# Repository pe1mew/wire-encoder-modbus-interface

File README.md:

# Wire Encoder Modbus Interface

A CH32V003-based interface board that measures **how far a window is open**
and publishes it on **Modbus RTU over RS-485**, powered by 24 V passive PoE
and designed for daisy-chained field buses.

The measurement comes from a **draw-wire encoder**: a spring-loaded drum
pays out a steel wire attached to the moving window frame, and the drum
turns a **10 kΩ potentiometer**. The wiper voltage is therefore an absolute
measure of the opening — valid the instant power returns, with no homing
move and no count to lose.

Two end-of-travel switches report that the window has reached a mechanical
stop, read as a supervised resistor ladder that also monitors its own cable.

One firmware build, addressed by a PC1 solder jumper:

| Jumper open | Jumper bridged |
|---|---|
| **40** | 45 |

The 40/45 pair is deliberately clear of the sibling
[`windmeters-modbus-interface`](https://github.com/pe1mew/windmeters-modbus-interface)
family (30–37), so both can share one RS-485 segment.

## Project status (2026-09-05)

| Area | State |
|---|---|
| Requirements | [`design/TDS.md`](design/TDS.md) **v0.7** — **79 requirements** (28 FR-MB, 20 FR-S, 23 FR-E, 8 NFR), every one traced to a test row and **gate-enforced** by `software/hil/acceptance/test_traceability.py` |
| Drivers | Modbus RTU + debug UART carried over HIL-verified; the encoder driver (`software/drivers/wire_encoder/`) is **written, verified and integrated** |
| Product firmware | **Complete.** Integration stages **A–F done** ([`design/integrationPlan.md`](design/integrationPlan.md)) — measurement, averaging, persistence and sensing health. 6 364 B flash (44 %), 1 108 B RAM (62 %). A healthy device reports status `0x0000` |
| Hardware/HIL | Schematic and PCB layout in `hardware/KiCad/`; the build under test is still a **breadboard**, so every Group A result carries that caveat. HIL rig complete: ADALM2000 RS-485 master, Saleae Logic16, and a built window emulator |
| Testing | 3 host suites (`scale`, `avg`, `health`), 27 HIL scripts, 11 acceptance tests. Results in [`software/hil/testReport.md`](software/hil/testReport.md) |
| Blocked | Four items, all on **instruments, not code**: adjustable PSU (±15 % supply margin, TP-A03/TP-B23 — the tightest unmeasured number), a PCB (TP-B36), a precision resistance box (FR-E03), a 5 ms bounce injector (FR-E15) |
| Release | No firmware version tagged yet; `fw-v1` is a candidate pending the above ([`software/firmware/RELEASES.md`](software/firmware/RELEASES.md)) |

## Hardware

The board reuses the sibling project's design wholesale apart from the
sensor front-end:

- **MCU**: WCH CH32V003J4M6 (RISC-V, SOP-8, 16 KB flash / 2 KB RAM). The
  8-pin package drives the whole design: single-wire UART discipline, remap
  tricks, and a zero-interrupt firmware architecture
  ([`design/softwareArchitecture.md`](design/softwareArchitecture.md)).
- **RS-485**: MAX3485; DI+RO tied to PD6, DE+R̄Ē tied to PC2 with a 10 k
  pull-down (keeps the bus safe during reset/flashing); 120 Ω terminator
  behind a solder jumper; A/B fail-safe bias; SM712 TVS.
- **Power**: 24 V passive PoE on the spare pairs (4/5 = +, 7/8 = −) →
  DB207 bridge (polarity protection only) → HLK-K7803 buck → 3.3 V.
- **Sensor front-end**: the potentiometer wiper on PA2 (ADC ch0), read
  ratiometrically against VDD — no external reference, so supply ripple
  cancels. The end-switch ladder is on PC4 (ADC ch2).

**The pin budget is the binding constraint.** The SOP-8 package bonds
several GPIO onto shared pins (pin 1 is PD6 *and* PA1; pin 8 is PD1, PD4
*and* PD5), leaving **six physical I/O pins — and every one is committed**:
Modbus data, the wiper, DE/RE, the address jumper, the end-switch ladder,
SWIO. Note PC1 and PC4 are assigned the reverse of the obvious way: PC4
carries an ADC channel and PC1 does not, so the analog pin goes to the
switch loop and the boot-time address jumper takes the digital pin. Any
front-end idea that needs another pin does not fit. See
[`design/TDS.md`](design/TDS.md) §4.2.

## Modbus register map (summary)

12 input registers (FC04) and 6 holding registers (FC03/06/16). Inputs:
instantaneous and averaged opening, the minimum/maximum of the current
averaging window, the raw ADC code, status bits (including end-of-travel
reached and switch-loop fault), identification (build + firmware version),
uptime, CRC/served counters, seconds-since-last-valid-reading, and movement
rate. Holdings: zero offset,
measurement window, averaging window, full travel, and the two-point raw
calibration (raw code closed / raw code fully open) — so one image serves
any window, calibrated in the field over Modbus. All persisted in flash
across reset/power-loss; the defaults apply only on first boot / erased
store. The authoritative map with ranges, defaults and requirement IDs is
[`design/TDS.md`](design/TDS.md) §2.7/§2.8.

## Repository layout

| Path | Contents |
|---|---|
| [`design/`](design/README.md) | The design-document chain (index in [`design/README.md`](design/README.md)): scratchBook → description → TDS → softwareArchitecture (+ UML diagrams in `design/diagrams/`) → driverDevelopment → integrationPlan |
| `hardware/KiCad/` | Schematic + PCB (KiCad); symbol libraries as git submodules |
| `hardware/Documentation/` | Component datasheets (HLK-K78xx, DB20x, MAX3483/85, Kradex enclosure) |
| `software/firmware/` | Product firmware (PlatformIO + ch32v003fun): one release build, plus a bench-only test build |
| `software/drivers/` | Standalone driver projects with HIL test shells (the verified libraries the product references in place) |
| `software/hil/` | Scripted hardware-in-the-loop harness: Saleae Logic 2 (MCP) + ADALM2000 (libm2k) + `acceptance/` pytest suite |
| `Doxyfile` | Doxygen config — builds a single site (design docs + API reference) with this README as the landing page |
| `documentation/` | Chip pinout, programmer manual, and sensor reference material |

Clone with submodules:

```sh
git clone --recurse-submodules https://github.com/pe1mew/wire-encoder-modbus-interface.git
```

## Building and flashing

Requires [PlatformIO](https://platformio.org/) and a WCH-LinkE on SWIO.

```sh
cd software/firmware
pio run                            # the release build
pio run -t upload                  # flash via WCH-LinkE
```

`encoder_test` adds bench-only hooks — never release that binary. Resource
ceilings (14 336 B flash / 1 792 B RAM, NFR-RES01) are enforced as hard
build gates.
The firmware version byte lives in `src/version.h`; the release process is
documented in `RELEASES.md`.

## Testing

- **Acceptance suite** (bench: Saleae Logic 2 with its MCP server, ADALM2000,
  WCH-LinkE, TTL Modbus rig):

  ```sh
  cd software/hil/acceptance
  ..\.venv-m2k\Scripts\python.exe -m pytest .
  ```

  Only the build-gate rows are populated so far; the protocol and
  measurement rows arrive with the driver work. See
  [`software/hil/README.md`](software/hil/README.md) for instrument setup,
  wiring, and the bench-quirk catalogue.

## Documentation

- **What the device does** — [`design/description.md`](design/description.md)
  is the functional description in prose: sensing principle, what it
  reports, commissioning, fault behaviour, and the boundary of what it does
  not do. Start there.
- **Design record** — [`design/README.md`](design/README.md) indexes the
  document chain (requirements → architecture → drivers → integration) and
  the UML diagrams.
- **API + design site** — the firmware headers/sources carry full Doxygen,
  and [`Doxyfile`](Doxyfile) folds the design docs in as pages with this
  README as the landing page. Build the browsable HTML with:

  ```sh
  doxygen Doxyfile        # output in documentation/doxygen/html/index.html
  ```

## Related repositories

- [`pe1mew/windmeters-modbus-interface`](https://github.com/pe1mew/windmeters-modbus-interface) —
  the sibling project this repository is derived from: same MCU, same
  RS-485 front-end, same zero-ISR architecture, and the same potentiometer
  reading topology. Its Modbus RTU driver, board/persistence modules and
  HIL harness are carried over here, and its `design/` chain is the
  reference for anything not yet written down.
- [`pe1mew/windmeters-modbus-interface-tester`](https://github.com/pe1mew/windmeters-modbus-interface-tester) —
  the Modbus RTU master bench tool (M5Stack AtomS3 + RS-485) used to
  exercise devices in this family.

## License

Software is provided under a Source-Available Non-Commercial License;
documentation and images under CC BY-NC-ND 4.0. See [LICENSE](LICENSE) and
[license.md](license.md). Third-party datasheets and KiCad library
submodules remain under their owners' terms.

## Author

Remko Welling (PE1MEW)

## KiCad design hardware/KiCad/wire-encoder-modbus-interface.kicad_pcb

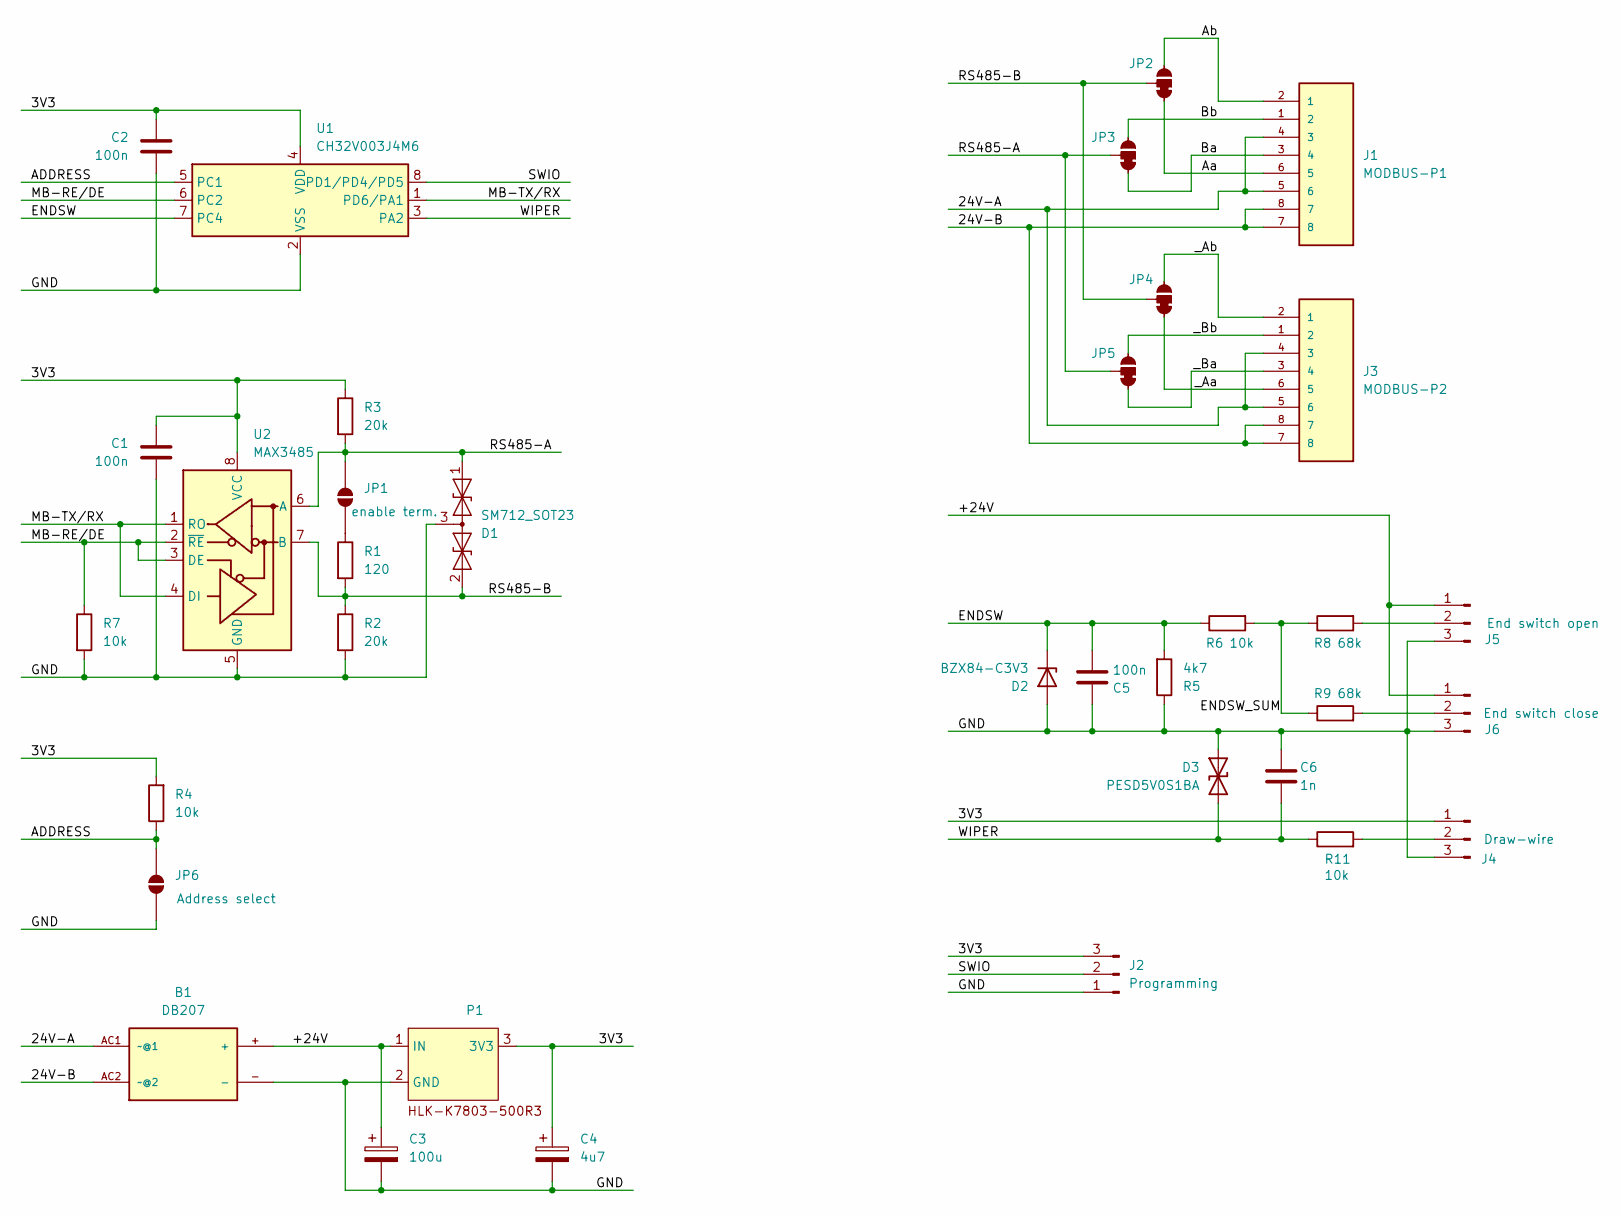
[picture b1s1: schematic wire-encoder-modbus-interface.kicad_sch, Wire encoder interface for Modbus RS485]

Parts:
B1: DB207; DB207-DIP-4
C1, C2, C5: 100n; C_1206_3216Metric_Pad1.33x1.80mm_HandSolder
C3: 100u; CP_Radial_D8.0mm_P5.00mm
C4: 4u7; CP_Radial_D5.0mm_P2.50mm
C6: 1n; C_1206_3216Metric_Pad1.33x1.80mm_HandSolder
D1: SM712_SOT23; SOT-23
D2: BZX84-C3V3; SOT-23
D3: PESD5V0S1BA; D_SOD-323_HandSoldering
J1: MODBUS-P1; CONN_215877-1; PARTREV AF1
J2: Programming; PinHeader_1x03_P2.54mm_Vertical
J3: MODBUS-P2; CONN_215877-1; PARTREV AF1
J4: Draw-wire; JST_NV_B03P-NV_1x03_P5.00mm_Vertical
J5: End switch open; JST_NV_B03P-NV_1x03_P5.00mm_Vertical
J6: End switch close; JST_NV_B03P-NV_1x03_P5.00mm_Vertical
JP1: enable term.; SolderJumper-2_P1.3mm_Open_Pad1.0x1.5mm
JP2, JP3, JP4, JP5: SolderJumper-3_P1.3mm_Bridged12_Pad1.0x1.5mm_NumberLabels
JP6: Address select; SolderJumper-2_P1.3mm_Open_Pad1.0x1.5mm
P1: HLK-K7803-500R3
R1: 120; R_1206_3216Metric_Pad1.30x1.75mm_HandSolder
R2, R3: 20k; R_1206_3216Metric_Pad1.30x1.75mm_HandSolder
R4, R6, R7, R11: 10k; R_1206_3216Metric_Pad1.30x1.75mm_HandSolder
R5: 4k7; R_1206_3216Metric_Pad1.30x1.75mm_HandSolder
R8, R9: 68k; R_1206_3216Metric_Pad1.30x1.75mm_HandSolder
U1: CH32V003J4M6; JEITA_SOIC-8_3.9x4.9mm_P1.27mm
U2: MAX3485; SOIC-8_3.9x4.9mm_P1.27mm

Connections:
/3V3: C1.1, C2.1, C4.1, J2.3, J4.1, P1.3 (3V3), R3.1, R4.2, U1.4 (VDD), U2.8 (VCC)
/24V-A: B1.AC1 (~@1), J1.4 (3), J1.5 (6), J3.4 (3), J3.5 (6)
/24V-B: B1.AC2 (~@2), J1.7 (8), J1.8 (7), J3.7 (8), J3.8 (7)
/+24V: B1.+, C3.1, J5.1, J6.1, P1.1 (IN)
/ADDRESS: JP6.2 (B), R4.1, U1.5 (PC1)
/Aa: J1.6 (5), JP2.1 (A)
/Ab: J1.2 (1), JP2.3 (C)
/Ba: J1.3 (4), JP3.1 (A)
/Bb: J1.1 (2), JP3.3 (C)
/ENDSW: C5.2, D2.3 (K), R5.2, R6.1, U1.7 (PC4)
/ENDSW_SUM: R6.2, R8.1, R9.1
/GND: B1.-, C1.2, C2.2, C3.2, C4.2, C5.1, C6.1, D1.3 (common), D2.1 (A), D3.1 (A1), J2.1, J4.3, J5.3, J6.3, JP6.1 (A), P1.2 (GND), R2.2, R5.1, R7.2, U1.2 (VSS), U2.5 (GND)
/MB-RE/DE: R7.1, U1.6 (PC2), U2.2 (~RE), U2.3 (DE)
/MB-TX/RX: U1.1 (PD6/PA1), U2.1 (RO), U2.4 (DI)
/RS485-A: D1.1 (A1), JP1.2 (B), JP3.2 (B), JP5.2 (B), R3.2, U2.6 (A)
/RS485-B: D1.2 (A2), JP2.2 (B), JP4.2 (B), R1.2, R2.1, U2.7 (B)
/SWIO: J2.2, U1.8 (PD1/PD4/PD5)
/WIPER: C6.2, D3.2 (A2), R11.1, U1.3 (PA2)
/_Aa: J3.6 (5), JP4.1 (A)
/_Ab: J3.2 (1), JP4.3 (C)
/_Ba: J3.3 (4), JP5.1 (A)
/_Bb: J3.1 (2), JP5.3 (C)
unnamed: J4.2, R11.2
unnamed: J5.2, R8.2
unnamed: J6.2, R9.2
unnamed: JP1.1 (A), R1.1

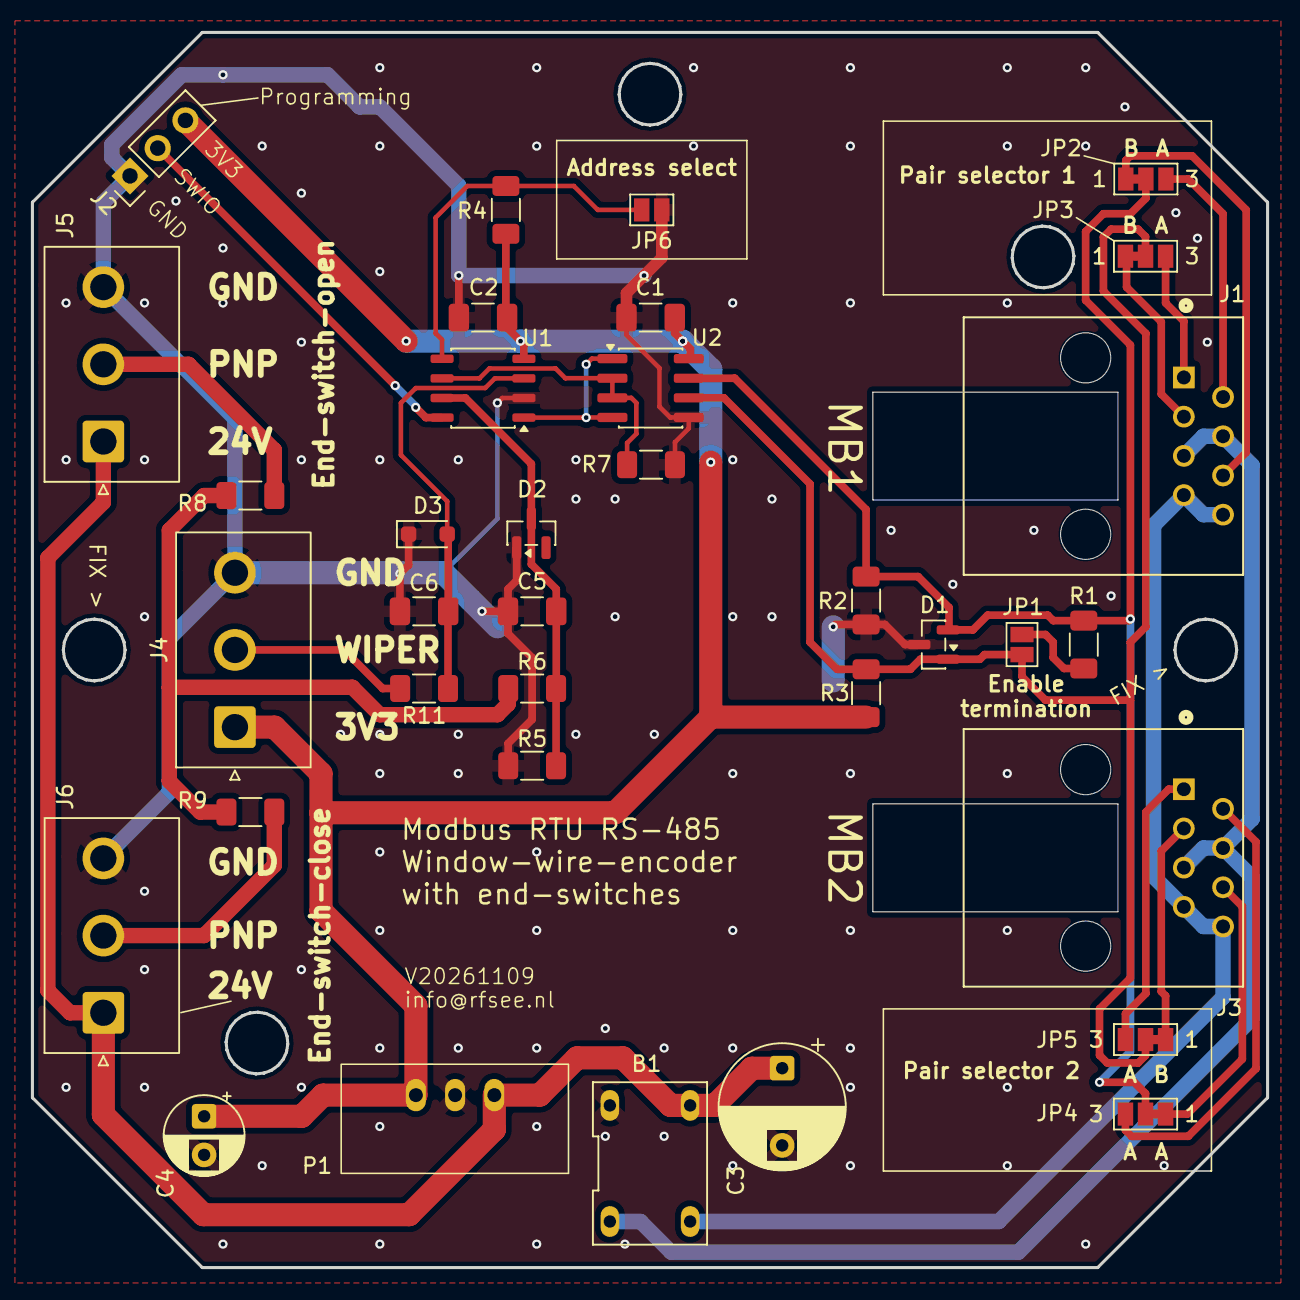
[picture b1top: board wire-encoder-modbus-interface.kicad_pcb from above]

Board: 2 copper layers, 80.0 x 80.0 mm, 35 parts (0 on the bottom side), 26 nets.

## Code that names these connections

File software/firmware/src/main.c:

/*
 * Wire encoder Modbus interface — product firmware (CH32V003J4M6, SOIC-8)
 *
 * Measures how far a window is open. A draw-wire encoder attached to the moving
 * frame turns a 10 kΩ potentiometer; the wiper is read ratiometrically on PA2
 * and published over Modbus RTU (TDS §1.1, §3.4).
 *
 * Zero-ISR cooperative super-loop (design/softwareArchitecture.md).
 * Stage D state (design/integrationPlan.md): board bring-up, the register image
 * (regs.c), flash persistence, the encoder driver (we.c) and the measurement
 * service (meas_open.c) are all in place, so 30001/30005/30012/30015 and status
 * bits 2/3/4 are live. Still missing is stage E — the averaging engine — so
 * 30002 (mean) and 30003/30004 (window min/max) do not yet update and status
 * bit 1 stays set.
 *
 * Assumed pin map (TDS §4.2 — no schematic exists yet): PD6 Modbus line
 * (remap-switching discipline, no HDSEL), PA2 potentiometer wiper (ADC ch0),
 * PC2 DE/R̄Ē, PC1 address jumper, PC4 end-switch divider (ADC ch2), PD1 SWIO.
 * Every pin is committed; PC1/PC4 are assigned the reverse of the obvious way
 * because PC4 has an ADC channel and the switch divider needs it.
 */

#include "board.h"
#include "ch32fun.h"
#include "mb.h"
#include "meas_open.h"
#include "regs.h"
#include "sensors.h"
#include "we.h"

int main(void)
{
	SystemInit();
	funGpioInitAll();

	/* FR-S18 init order:
	 * (1) PC2/DE low first + (2) PC1 address latch + IWDG + PVD ... */
	board_init_early();

	/* FR-S18 (3): sensor front-end ready. Before regs_init, so the ADC
	 * self-calibration is complete before anything can read a register. */
	we_init();

	/* regs_init loads the persisted holdings (FR-S39) BEFORE the measurement
	 * service latches the window, so the first window already uses the stored
	 * duration — no spurious first-window abort at boot. */
	regs_init(board_mb_address());

	/* The measurement service latches 40002 AFTER regs_init has loaded the
	 * persisted holdings, so the first window already runs at the stored
	 * duration and does not abort itself on the first pass (FR-S30). */
	meas_open_init();

	/* (4) USART receiver enabled last. */
	mb_init(regs_cfg());

	const uint32_t second_ticks = FUNCONF_SYSTEM_CORE_CLOCK;
	uint32_t t_second = SysTick->CNT;

	while (1)
	{
		mb_poll();
		regs_service();          /* FR-S30/FR-E05: config change -> clear */
		regs_persist_service();  /* FR-S39: save changed settings to flash
		                          * (after mb_poll sent any response) */

		/* Window pacing, wiper and ladder sampling, FR-E04 scaling and
		 * publication. Placed after regs_persist_service so a flash write
		 * never sits between a sample and its publication. */
		meas_open_service();

		if ((uint32_t)(SysTick->CNT - t_second) >= second_ticks)
		{
			t_second += second_ticks;
			regs_second_tick();
		}

#ifdef TEST_HOOKS
		if (regs_test_hang_requested())
			for (;;)
				; /* FR-S20 test: stop servicing AND feeding — dog bites */
#endif
		/* FR-S20: refresh only here, at the end of a full loop pass, and
		 * only while the rail is healthy (FR-S22). */
		if (board_power_ok())
			board_iwdg_feed();
	}
}
